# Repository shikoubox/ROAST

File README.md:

DTU Roadrunners Solar Team

Code and source files for all Solar Car parts and other related files. (e.g. PCBs, 3D prints, Embedded, Project materials, datasheets and literature)

# Structure
For parts, put all relevant for your part/project in a corresponding parts folder with, part and year.
For files that are larger than 100 MB, please upload them to OneDrive instead, and leave a link if relevant in this repository.

# CAD
All CAD is done in Solidworks.
Please provide technical drawings in .pdf, to avoid need for SolidWorks.

# Circuit Boards
All PCB design is done in KiCad.
There are old projects done in Eagle, but Autodesk has killed the Eagle.
Please provide schematics in .pdf, to avoid need for KiCad or Eagle, to see the circuit/board layout.

Also, both pdf, project, and silkscreen needs a tag with appropriate PCB title, date, revision no., and who made it (e.g. study number).

# Communication, discussion and questions
Please use the discord:
https://discord.gg/Wzs3dZkhpT

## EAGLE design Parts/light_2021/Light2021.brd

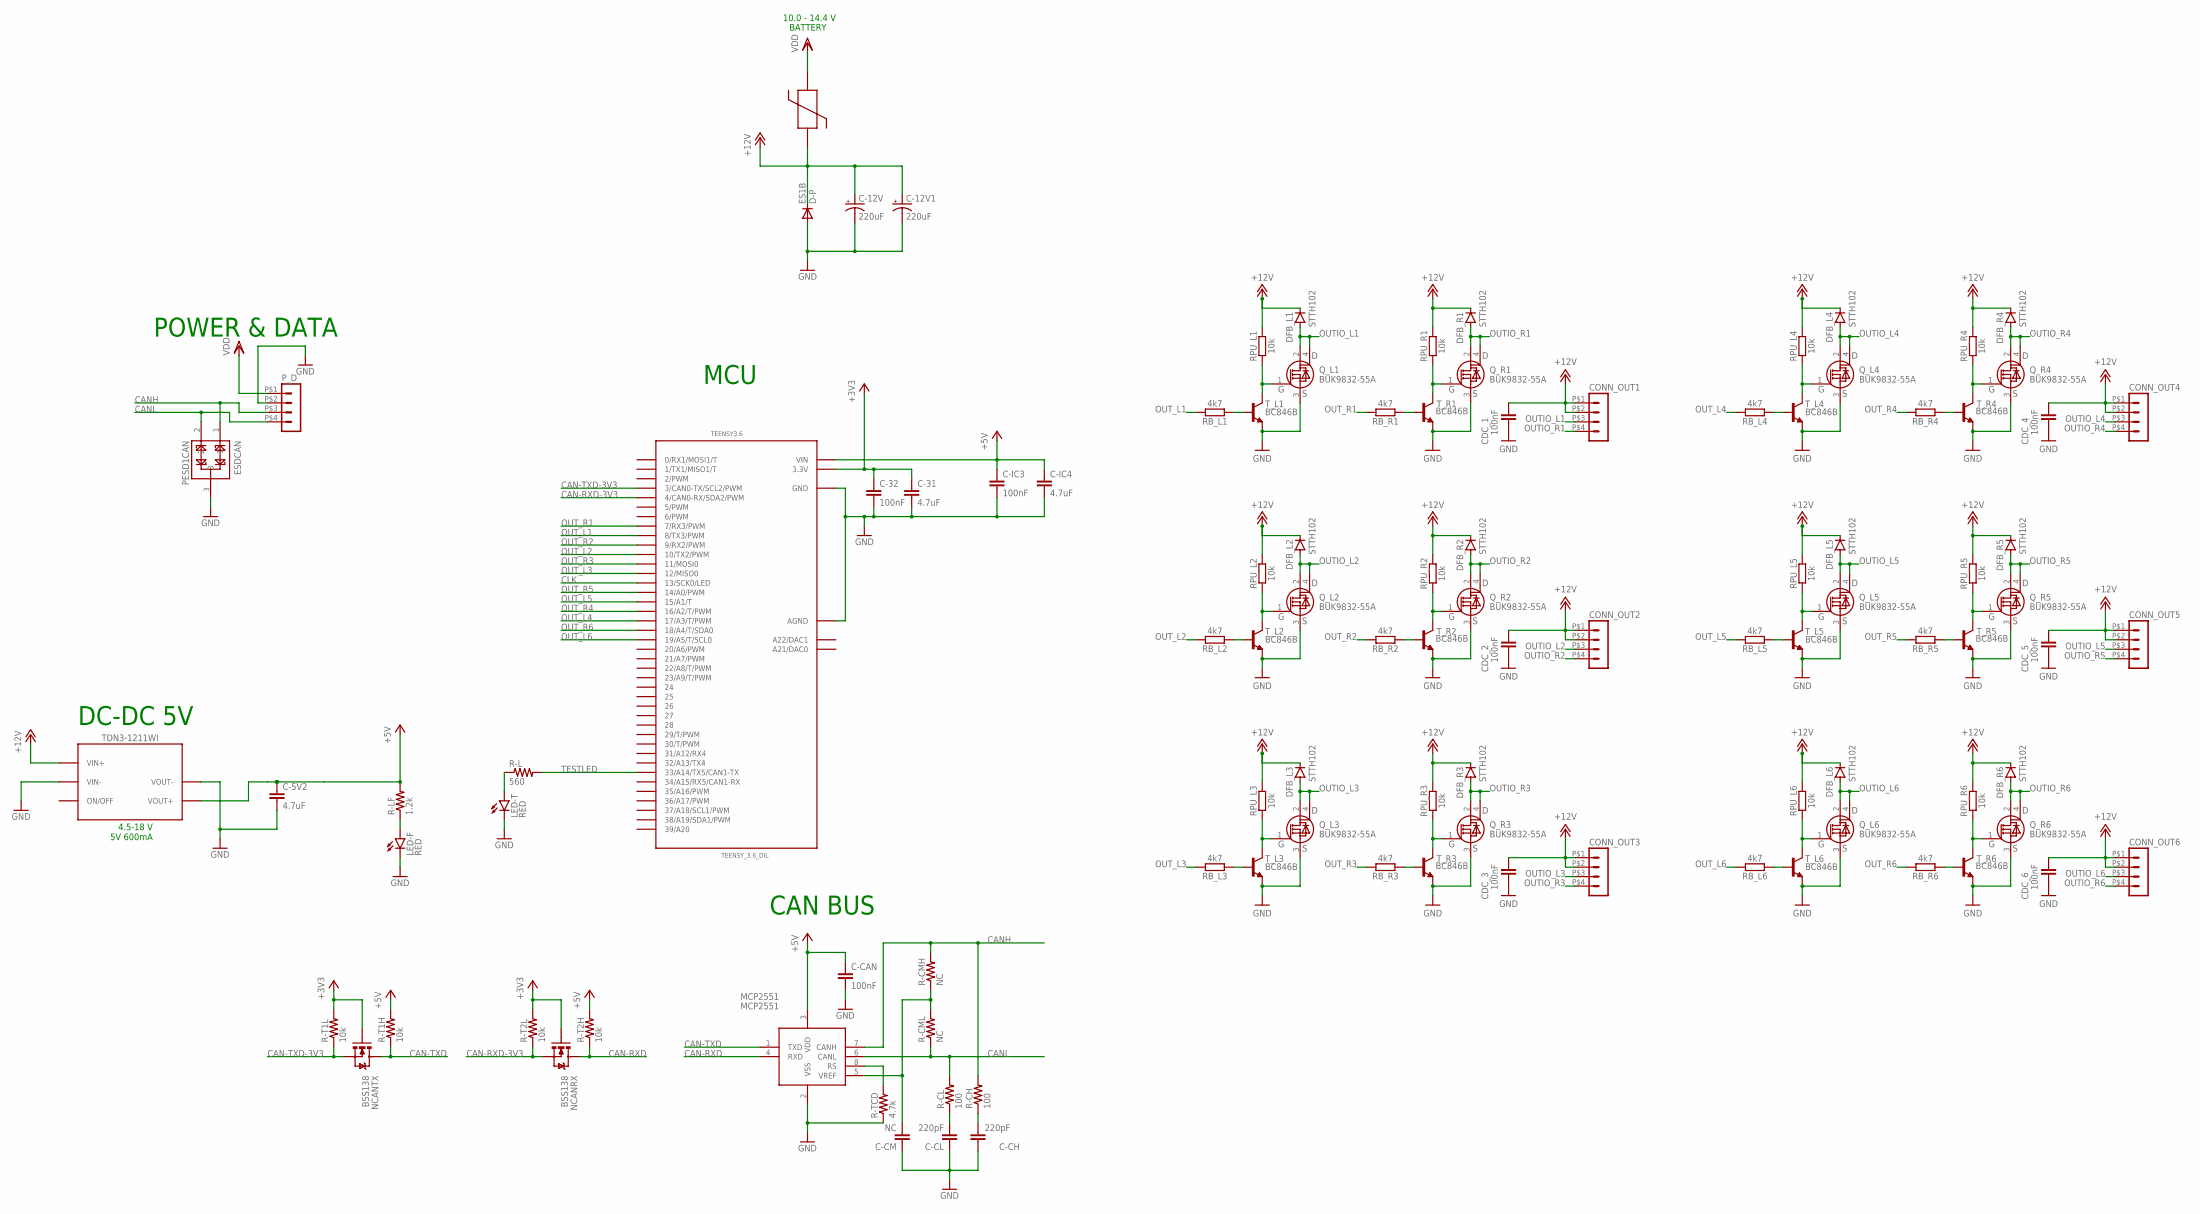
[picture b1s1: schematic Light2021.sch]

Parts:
C-5V2, C-31: 4.7uF; 1210
C-12V, C-12V1: 220uF; PANASONIC_D
C-32: 100nF; 0805
C-CAN: 100nF; 0805
C-CH: 220pF; 0805
C-CL: 220pF; 0805
C-CM: NC; 0805
C-IC3: 100nF; 0805
C-IC4: 4.7uF; 1210
CDC_1, CDC_2, CDC_3, CDC_4, CDC_5, CDC_6: 100nF; 0805
CONN_OUT1, CONN_OUT2, CONN_OUT3, CONN_OUT4, CONN_OUT5, CONN_OUT6: HEADER_POS4_43045-0401; 43045-0400
D-P: ES1B; SMA-DIODE
DFB_L1, DFB_L2, DFB_L3, DFB_L4, DFB_L5, DFB_L6: STTH102; DO214AC
DFB_R1, DFB_R2, DFB_R3, DFB_R4, DFB_R5, DFB_R6: STTH102; DO214AC
ESDCAN: PESD1CAN; SOT23-3
LED-F: RED; LED-1206
LED-T: RED; LED-1206
MAIN_FUSE: SMF_OMNI-BLOK_FUSE_BLOCK
MCP2551: MCP2551; SO-08M
NCANRX: BSS138; SOT23
NCANTX: BSS138; SOT23
P_D: HEADER_POS4_43045-0401; 43045-0400
Q_L1, Q_L2, Q_L3, Q_L4, Q_L5, Q_L6: BUK9832-55A; SOT230P700X180-4N
Q_R1, Q_R2, Q_R3, Q_R4, Q_R5, Q_R6: BUK9832-55A; SOT230P700X180-4N
R-CH: 100; 0805
R-CL: 100; 0805
R-CMH: NC; 0805
R-CML: NC; 0805
R-L: 560; 0805
R-LF: 1.2k; 0805
R-T1H, R-T1L, R-T2H, R-T2L: 10k; 0805
R-TCD: 4.7k; 0805
RB_L1, RB_L2, RB_L3, RB_L4, RB_L5, RB_L6: 4k7; R0805
RB_R1, RB_R2, RB_R3, RB_R4, RB_R5, RB_R6: 4k7; R0805
RPU_L1, RPU_L2, RPU_L3, RPU_L4, RPU_L5, RPU_L6: 10k; R0805
RPU_R1, RPU_R2, RPU_R3, RPU_R4, RPU_R5, RPU_R6: 10k; R0805
TDN3-1211WI: TDN3WI; TDC3WI
TEENSY3.6: TEENSY_3.6_DIL
T_L1, T_L2, T_L3, T_L4, T_L5, T_L6: BC846B; SOT23-BEC
T_R1, T_R2, T_R3, T_R4, T_R5, T_R6: BC846B; SOT23-BEC

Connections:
+3V3: C-31.1, C-32.1, NCANRX.1 (G), NCANTX.1 (G), R-T1L.2, R-T2L.2, TEENSY3.6.3.3V1 (3.3V), TEENSY3.6.3.3V2 (3.3V)
+5V: C-5V2.1, C-CAN.1, C-IC3.1, C-IC4.1, MCP2551.3 (VDD), R-LF.2, R-T1H.2, R-T2H.2, TDN3-1211WI.VOUT+, TEENSY3.6.VIN
+12V: C-12V.+, C-12V1.+, CDC_1.1, CDC_2.1, CDC_3.1, CDC_4.1, CDC_5.1, CDC_6.1, CONN_OUT1.P$1 (1), CONN_OUT1.P$2 (2), CONN_OUT2.P$1 (1), CONN_OUT2.P$2 (2), CONN_OUT3.P$1 (1), CONN_OUT3.P$2 (2), CONN_OUT4.P$1 (1), CONN_OUT4.P$2 (2), CONN_OUT5.P$1 (1), CONN_OUT5.P$2 (2), CONN_OUT6.P$1 (1), CONN_OUT6.P$2 (2), D-P.C, DFB_L1.C, DFB_L2.C, DFB_L3.C, DFB_L4.C, DFB_L5.C, DFB_L6.C, DFB_R1.C, DFB_R2.C, DFB_R3.C, DFB_R4.C, DFB_R5.C, DFB_R6.C, MAIN_FUSE.PIN1, RPU_L1.2, RPU_L2.2, RPU_L3.2, RPU_L4.2, RPU_L5.2, RPU_L6.2, RPU_R1.2, RPU_R2.2, RPU_R3.2, RPU_R4.2, RPU_R5.2, RPU_R6.2, TDN3-1211WI.VIN+
CAN-RXD: MCP2551.4 (RXD), NCANRX.3 (D), R-T2H.1
CAN-RXD-3V3: NCANRX.2 (S), R-T2L.1, TEENSY3.6.4 (4/CAN0-RX/SDA2/PWM)
CAN-TXD: MCP2551.1 (TXD), NCANTX.3 (D), R-T1H.1
CAN-TXD-3V3: NCANTX.2 (S), R-T1L.1, TEENSY3.6.3 (3/CAN0-TX/SCL2/PWM)
CANH: ESDCAN.1, MCP2551.7 (CANH), P_D.P$3 (3), R-CH.2, R-CMH.2
CANL: ESDCAN.2, MCP2551.6 (CANL), P_D.P$4 (4), R-CL.2, R-CML.1
CLK: TEENSY3.6.13 (13/SCK0/LED)
GND: C-5V2.2, C-12V.-, C-12V1.-, C-31.2, C-32.2, C-CAN.2, C-CH.1, C-CL.1, C-CM.1, C-IC3.2, C-IC4.2, CDC_1.2, CDC_2.2, CDC_3.2, CDC_4.2, CDC_5.2, CDC_6.2, D-P.A, ESDCAN.3, LED-F.C, LED-T.C, MCP2551.2 (VSS), P_D.P$2 (2), Q_L1.3 (S), Q_L2.3 (S), Q_L3.3 (S), Q_L4.3 (S), Q_L5.3 (S), Q_L6.3 (S), Q_R1.3 (S), Q_R2.3 (S), Q_R3.3 (S), Q_R4.3 (S), Q_R5.3 (S), Q_R6.3 (S), R-TCD.1, TDN3-1211WI.VIN-, TDN3-1211WI.VOUT-, TEENSY3.6.AGND, TEENSY3.6.GND, TEENSY3.6.GND1 (GND), T_L1.E, T_L2.E, T_L3.E, T_L4.E, T_L5.E, T_L6.E, T_R1.E, T_R2.E, T_R3.E, T_R4.E, T_R5.E, T_R6.E
unnamed: LED-T.A, R-L.1
unnamed: C-CM.2, MCP2551.5 (VREF), R-CMH.1, R-CML.2
unnamed: RB_L1.1, T_L1.B
unnamed: Q_L1.1 (G), RPU_L1.1, T_L1.C
unnamed: RB_R1.1, T_R1.B
unnamed: Q_R1.1 (G), RPU_R1.1, T_R1.C
unnamed: RB_L2.1, T_L2.B
unnamed: LED-F.A, R-LF.1
unnamed: Q_L2.1 (G), RPU_L2.1, T_L2.C
unnamed: RB_R2.1, T_R2.B
unnamed: Q_R2.1 (G), RPU_R2.1, T_R2.C
unnamed: RB_L3.1, T_L3.B
unnamed: Q_L3.1 (G), RPU_L3.1, T_L3.C
unnamed: RB_R3.1, T_R3.B
unnamed: Q_R3.1 (G), RPU_R3.1, T_R3.C
unnamed: RB_L4.1, T_L4.B
unnamed: C-CL.2, R-CL.1
unnamed: C-CH.2, R-CH.1
unnamed: Q_L4.1 (G), RPU_L4.1, T_L4.C
unnamed: RB_R4.1, T_R4.B
unnamed: Q_R4.1 (G), RPU_R4.1, T_R4.C
unnamed: RB_L5.1, T_L5.B
unnamed: Q_L5.1 (G), RPU_L5.1, T_L5.C
unnamed: RB_R5.1, T_R5.B
unnamed: Q_R5.1 (G), RPU_R5.1, T_R5.C
unnamed: RB_L6.1, T_L6.B
unnamed: Q_L6.1 (G), RPU_L6.1, T_L6.C
unnamed: RB_R6.1, T_R6.B
unnamed: Q_R6.1 (G), RPU_R6.1, T_R6.C
OUTIO_L1: CONN_OUT1.P$3 (3), DFB_L1.A, Q_L1.2 (D), Q_L1.4 (D)
OUTIO_L2: CONN_OUT2.P$3 (3), DFB_L2.A, Q_L2.2 (D), Q_L2.4 (D)
OUTIO_L3: CONN_OUT3.P$3 (3), DFB_L3.A, Q_L3.2 (D), Q_L3.4 (D)
OUTIO_L4: CONN_OUT4.P$3 (3), DFB_L4.A, Q_L4.2 (D), Q_L4.4 (D)
OUTIO_L5: CONN_OUT5.P$3 (3), DFB_L5.A, Q_L5.2 (D), Q_L5.4 (D)
OUTIO_L6: CONN_OUT6.P$3 (3), DFB_L6.A, Q_L6.2 (D), Q_L6.4 (D)
OUTIO_R1: CONN_OUT1.P$4 (4), DFB_R1.A, Q_R1.2 (D), Q_R1.4 (D)
OUTIO_R2: CONN_OUT2.P$4 (4), DFB_R2.A, Q_R2.2 (D), Q_R2.4 (D)
OUTIO_R3: CONN_OUT3.P$4 (4), DFB_R3.A, Q_R3.2 (D), Q_R3.4 (D)
OUTIO_R4: CONN_OUT4.P$4 (4), DFB_R4.A, Q_R4.2 (D), Q_R4.4 (D)
OUTIO_R5: CONN_OUT5.P$4 (4), DFB_R5.A, Q_R5.2 (D), Q_R5.4 (D)
OUTIO_R6: CONN_OUT6.P$4 (4), DFB_R6.A, Q_R6.2 (D), Q_R6.4 (D)
OUT_L1: RB_L1.2, TEENSY3.6.8 (8/TX3/PWM)
OUT_L2: RB_L2.2, TEENSY3.6.10 (10/TX2/PWM)
OUT_L3: RB_L3.2, TEENSY3.6.12 (12/MISO0)
OUT_L4: RB_L4.2, TEENSY3.6.17/A3 (17/A3/T/PWM)
OUT_L5: RB_L5.2, TEENSY3.6.15/A1 (15/A1/T)
OUT_L6: RB_L6.2, TEENSY3.6.19/A5 (19/A5/T/SCL0)
OUT_R1: RB_R1.2, TEENSY3.6.7 (7/RX3/PWM)
OUT_R2: RB_R2.2, TEENSY3.6.9 (9/RX2/PWM)
OUT_R3: RB_R3.2, TEENSY3.6.11 (11/MOSI0)
OUT_R4: RB_R4.2, TEENSY3.6.16/A2 (16/A2/T/PWM)
OUT_R5: RB_R5.2, TEENSY3.6.14/A0 (14/A0/PWM)
OUT_R6: RB_R6.2, TEENSY3.6.18/A4 (18/A4/T/SDA0)
RS: MCP2551.8 (RS), R-TCD.2
TESTLED: R-L.2, TEENSY3.6.33/A14 (33/A14/TX5/CAN1-TX)
VDD: MAIN_FUSE.PIN2, P_D.P$1 (1)

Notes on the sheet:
MCU
BATTERY
10.0 - 14.4 V
CAN BUS
POWER & DATA
DC-DC 5V
4.5-18 V 5V 600mA

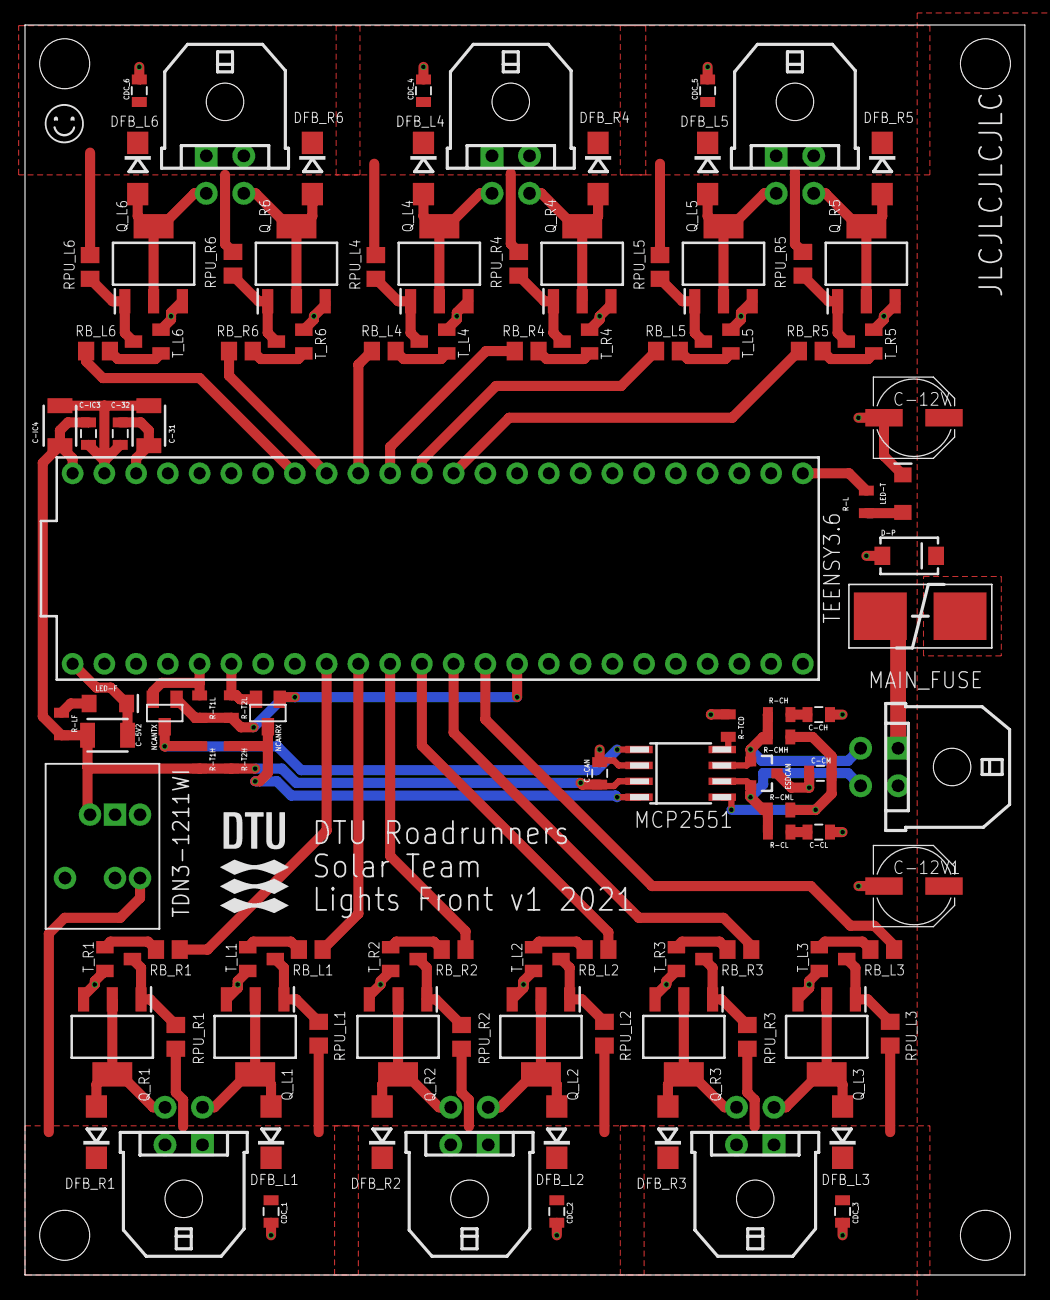
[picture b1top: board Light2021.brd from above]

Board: 2 copper layers, 80.0 x 100.0 mm, 108 parts (1 on the bottom side), 66 nets.

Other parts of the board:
U$1: DTU-SMALL-5MM
U$2: SMILEY
U$3: DTU-MEDIUM-9MM-BOTTOM

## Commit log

2025-01-24 PCB
    A WIP PCB for the rat
2025-01-24 Rename gitignore to .gitignore
2025-01-27 backup
2025-01-28 pcb backup
2025-01-28 Organising parts folder
2025-01-28 Button_code
2025-01-28 Renamed files containing Ø
2025-01-28 Updated last files with uncommon symbols
2025-01-28 Trying to remove nasty files
2025-01-28 pcb progress backup
2025-01-29 PCB v1
2025-01-29 KiCad after review 1
    Spinat skal hjem og gro, Ost tager over og arbejder videre efter hans gode første review.
2025-01-29 KiCad cheatsheet
2025-01-29 Kicad drawing update
2025-01-31 Trying to fix bad naming again.
2025-01-31 slight changes in schematic
2025-01-31 Trying to add the deleted files
2025-01-31 Trying to remove them again
2025-01-31 trying to remove dead files
2025-01-31 Deleted remaining dead files
2025-01-31 Deleted last dead file and renamed telemetry folders, according to their year.
2025-01-31 PCB work update
2025-02-20 All versions
    All versions from prototype 0.1 to final V5 with raw files.
2025-02-20 removed unneeded
2025-03-25 Telemetry_2024_pdf
    + Patch antenna project
2025-04-24 Dashboard electron
2025-05-30 Updated the project so it reads values from a .csv file
2025-05-30 css update to be lil bigger text
2025-06-04 Initial commit on orphan branch
2025-06-04 Added dashboard folder
2025-06-05 Readme updates
2025-06-05 paste
2025-06-06 Update to dashboard
2025-06-06 Updated_names + csv
2025-06-06 Pulled dashboard to pi_dashboard
2025-06-06 Included the new data.csv
2025-06-09 Update to dashboard
    add data.py
2025-06-09 Radio setup scripts
2025-06-09 More changes to README
2025-06-09 Revisioned version of RFM script
2025-06-09 Better version of the rfm69hcw .py script
2025-06-09 git notes to README
2025-06-09 RF changes
2025-06-09 Cleanup and try to automatise
2025-06-09 Error correction
2025-06-09 Bug fixes
2025-06-09 Bug fixes?
2025-06-09 adding the commit
2025-06-09 update pin
2025-06-10 Dashboard_update.V2.1
    Data.py + css
2025-06-10 rfm69 update
2025-06-10 Fix readme and more changes to RFM module
2025-06-10 More changes and tweaks to RFM code
2025-06-10 rfm69hcw small change
2025-06-10 Better version of the rfm69hcw.py script
2025-06-10 updating rfm69hcw for test on pi
2025-06-10 Test new setup
2025-06-10 main.js go faster
2025-06-10 Revert "updating rfm69hcw for test on pi"
    This reverts commit 7bb67f8a7294224f21d582e892c468cbdaad0d15.
2025-06-11 deleted unused files, and removed csv handling from _rfm69hcw.py
2025-06-11 update.V0
2025-06-11 pieces of code
2025-06-11 new_code_update_CSV
    Error handeling
2025-06-11 Log and update feature
2025-06-11 update main.js 10/sek
2025-06-11 Moved data manipulation to different script
2025-06-11 Decoding capability
2025-06-11 fixed data manipulation error
2025-06-11 Trying to move curses into curses file
2025-06-11 Fixing curses bugs
2025-06-11 Try to fix RF responsibility
2025-06-11 RF bug test
2025-06-11 update to byte handler
2025-06-11 Correct byte handling
2025-06-11 typo
2025-06-12 Send test packet to csv handler
2025-06-12 Send test packet to csv byte handler
2025-06-12 bug fix
2025-06-12 bug fix test
2025-06-12 test
2025-06-12 stable
2025-06-12 test if bug was fixed
2025-06-12 Try with try:
2025-06-12 Fixing blunder
2025-06-12 Renaming files
2025-06-12 Moved files, and updated files
2025-06-12 updated initialisation of rfm69
2025-06-12 Fixing .csv to include bytearrays
2025-06-12 less debugs
2025-06-13 Updated electron app looks
2025-06-13 dBm added to the electron app
2025-06-13 Moved buttons to a more sensical place
2025-06-13 Updated files, without testing them, for rssi capabilities, and cleaner code
2025-06-13 Bug fix attempt
2025-06-13 added .gitignore as well as fixed float int confusion
2025-06-13 fix small mistake
2025-06-13 index error fix
2025-06-17 Fixed and updated README.md
2025-06-25 updated data and styles for a picture in report
2025-06-29 Try to fix responsibilities
2025-06-29 extra plebs
2025-07-07 dashboard update
2025-07-07 Updates to radio_module.py for testing
2025-07-13 fixed structure and text
2025-07-13 radio_module.py, added comments
2025-07-13 Updated text in index and renderer
2025-07-13 Comments on rfm69_utils
2025-07-13 update text in handler and data
2025-07-15 graphics changes
2025-07-15 Encoding.py
2025-07-15 Update: graphics, radio_module and rfm69_utils
2025-07-15 update text
2025-07-15 More comments to csv_handler
2025-07-16 Error fixing with kicad_dru, and silkscreeen updates. TO-DO: BOM to basic
2025-08-01 board update
2025-08-01 3D_files_rat
2025-08-01 PCB_Remake
2025-08-01 Rename folders for consistency
2025-08-01 updated .gitignore
2025-08-26 Rename Aflevering (1).pdf to light_system_introductory_project_report_2022

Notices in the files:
parts and their libraries:
SparkFun-Resistors: Licensing: CC v3.0 Share-Alike You are welcome to use this library for commercial purposes.
